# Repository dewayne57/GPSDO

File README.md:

# GPSDO (GPS Disciplined Oscillator)

This repository contains a hardware and firmware design for a GPS-disciplined oscillator (GPSDO). The system uses
a local oven-controlled crystal oscillator (OCXO) disciplined by a GPS reference (1PPS and time) via a digital control
loop implemented on a PIC microcontroller.

Purpose: provide a compact, buildable GPSDO that combines the short-term stability of an OCXO with the long-term
accuracy of GPS. The design favors through-hole assembly and flexible OCXO support so hobbyists and technicians can
adapt the board to available oscillators.

**Repository layout**
- `Hardware/`: KiCad schematics and PCB files, and OCXO compatibility notes.
- `Software/`: PIC firmware source (`main.c`, `isr.c`, config and peripheral drivers).

**Key features**
- Uses a PIC18F series microcontroller for the digital control loop and measurement counters.
- Supports 5 V and 12 V OCXO modules with jumper-selectable scaling.
- External DAC (12-bit) for fine VCO control; optional use of OCXO internal reference.
- Sine-to-square conversion option for sine-output OCXOs.
- Outputs: 10 MHz (square), 1PPS, and serial time/status (where supported).

Hardware notes
- OCXO compatibility: designed for OCXO modules that expose a VCO (frequency adjust) input. Modules without a VCO
	pin are not supported.
- Recommended OCXO families (examples): Bliley N47/NV47, IsoTemp 141 A/N, Vectron C4550, Oscilloquartz 8663.
- VCO adjustment: typical adjustment ranges are on the order of ±0.4 to ±1.0 ppm. For a 10 MHz OCXO, ±0.4 ppm
	corresponds to about ±4 Hz of pull range.
- Voltage reference: jumpers allow either the OCXO's onboard reference or the microcontroller-supplied reference to be
	used for VCO control circuitry.
- Power: supports 5 V and 12 V OCXO modules. The design omits 3.3 V OCXO variants to keep voltage-scaling circuitry
	simpler.

Firmware and control
- The PIC microcontroller implements the digital disciplining loop: it measures phase/frequency against GPS 1PPS and
	computes corrections applied through the DAC to the OCXO VCO input.
- Communication: firmware includes basic status reporting via serial (see `Software/` source files).

## Theory of Operation

Overview
- The system uses the PIC18F's high-speed signal acquisition timer/counter to measure the OCXO frequency against the GPS
	1PPS reference. The 10 MHz output from the OCXO (after conditioning through comparator or buffering as needed) is fed
	into the controller's counter. Each rising edge of the 1PPS signal triggers a capture of the counter value.

Measurement and error calculation
- The counter measurement produces the number of 10 MHz cycles counted during one 1-second interval. For an ideal
	10 MHz oscillator the measured count is 10,000,000. The firmware computes the frequency error as:

	`error = measured_count - 10,000,000`

- Control action sign: when `measured_count > 10,000,000` (oscillator fast) the firmware decreases the DAC output
	(reducing VCO control voltage) to lower the oscillator frequency. Conversely, when `measured_count < 10,000,000`
	(oscillator slow) the firmware increases the DAC output to raise the frequency.

Resolution and averaging
- A single 1-second count has 1 Hz quantization (one extra or missing cycle = ±1 Hz). Because the OCXO VCO pull range
	is often a few Hz, and long-term stability targets are well below 1 Hz, the firmware uses averaging and filtering
	across multiple 1‑second samples to resolve sub-Hz frequency offsets. Averaging N seconds reduces quantization noise by
	roughly `1/sqrt(N)` for uncorrelated noise and linearly for simple accumulation.

Digital control loop
- The control loop is implemented in firmware and is PID-like: it applies a proportional term (responds to the
	instantaneous frequency error), an integral term (eliminates steady-state offset over time) and optional damping
	(derivative-like or filtered difference) to stabilize transient responses.
- To avoid overshoot and instability, the loop includes:
	- limited update rate and maximum DAC-step per update,
	- anti-windup on the integrator when the DAC saturates,
	- configurable loop bandwidth (slow for best long-term stability, faster during initial acquisition).

Noise and spurious rejection
- Input conditioning: if the OCXO provides a sine output, it is converted to a clean logic edge via the comparator and
	Schmitt trigger chain (comparator `U401`, logic buffers), which reduces timing jitter and false counts.
- Outlier rejection: the firmware detects and ignores single-sample glitches (spikes) using median filters, clamp
	thresholds, or by discarding samples with implausible changes.
- Low-pass filtering: measurement samples are filtered (moving average or IIR) before being fed into the control law to
	reject short-term noise and spurious phase jitter from the GPS receiver or RF pickup.

DAC mapping and VCO sensitivity
- The external DAC (12-bit) produces the control voltage applied to the OCXO VCO pin (optionally scaled by jumper
	networks for 5/12 V OCXOs). The frequency change per DAC LSB depends on the OCXO sensitivity (Hz per volt). The
	firmware maps desired frequency correction to DAC steps and can be configured for the measured sensitivity of a
	particular OCXO.
- Because frequency pull is small (few Hz), the DAC mapping and loop gains are tuned to provide fine, stable control
	without hunting.

Holdover and failure modes
- If GPS is lost, the firmware stops updating the DAC with GPS-derived corrections and enters a holdover mode. During
	holdover the DAC will be left at its last value.
- GPS lock is indicated by a front-panel LED.  If the GPS lock is lost, the operator should take the appropriate 
    actions to reposition or repair the GPS antenna.

Practical notes
- One-count resolution at 10 MHz corresponds to 1 Hz. To achieve sub-Hz apparent resolution the firmware averages and
	filters multiple 1PPS-captured counts before making DAC adjustments.
- Avoid using OCXO modules without an external VCO adjust pin — they cannot be disciplined by this design.
- Proper grounding, shielding, and clean supply rails reduce spurious counts and improve loop stability.

Build and usage
- Hardware: assemble the board following the silkscreen and BOM in `Hardware/`. Populate only the sections required for
	your chosen OCXO (jumper options allow omitting comparator/driver or scaling components).
- Antenna: mount the GPS antenna with a clear sky view; use a low-loss cable and proper grounding/lightning protection.
- Initial setup:
	1. Install firmware from `Software/` using a PIC programmer supporting the PIC18F family.
	2. Connect GPS antenna and power the board.
	3. Wait for GPS lock and allow the disciplining loop to converge (can take minutes to hours depending on configuration).
- Holdover: if GPS signal is lost, the OCXO runs free; holdover performance depends on the OCXO quality.

Testing and calibration
- Verify 1PPS and 10 MHz outputs with a frequency counter or scope.
- Observe DAC control voltage and confirm it stays within expected range while disciplining.
- Perform a holdover test by disconnecting GPS and measuring drift over a chosen interval.

Design considerations and limitations
- GPS vulnerability: system depends on GPS; consider anti-spoofing/jamming mitigation for critical deployments.
- Environmental sensitivity: OCXO performance varies with temperature — good thermal control improves holdover.

Contributing
If you improve the firmware, PCB, or documentation, please open an issue or a pull request. Include a short description
of your changes and validation steps.

License and credits
- This entire repository (software and hardware design files) is licensed under the Apache License, Version 2.0. See
  `LICENSE` at the repository root for the full text.
- If you incorporate third-party components with separate license requirements, include their required notices and
  follow the terms of those licenses.

Files of interest
- `Hardware/GPSDO.kicad_sch`, `Hardware/GPSDO.kicad_pcb`: primary schematic and PCB.
- `Software/main.c`, `Software/isr.c`, `Software/config.h`: firmware entry points and configuration.

Contact
Open issues in this repository or contact the author via the repository metadata for questions and contribution guidance.

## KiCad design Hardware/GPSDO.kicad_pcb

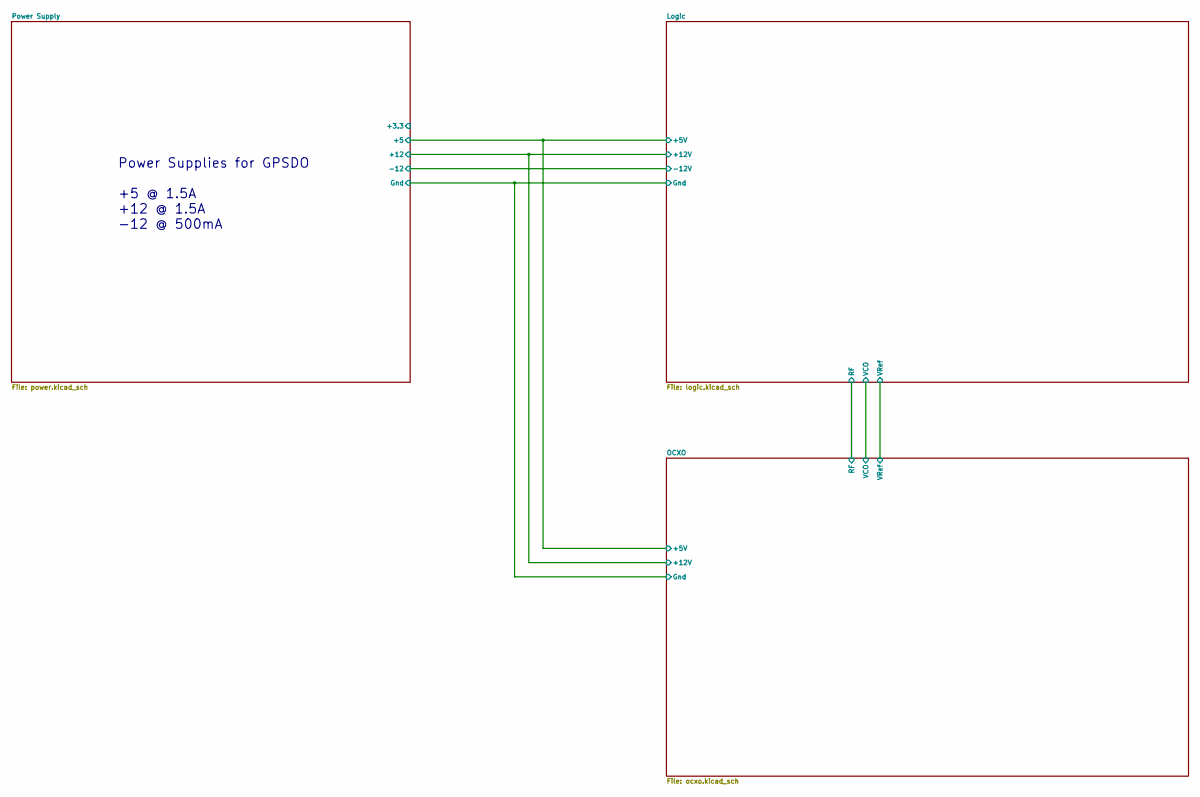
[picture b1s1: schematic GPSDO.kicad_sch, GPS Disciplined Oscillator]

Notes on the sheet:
Power Supplies for GPSDO +5 @ 1.5A +12 @ 1.5A -12 @ 500mA

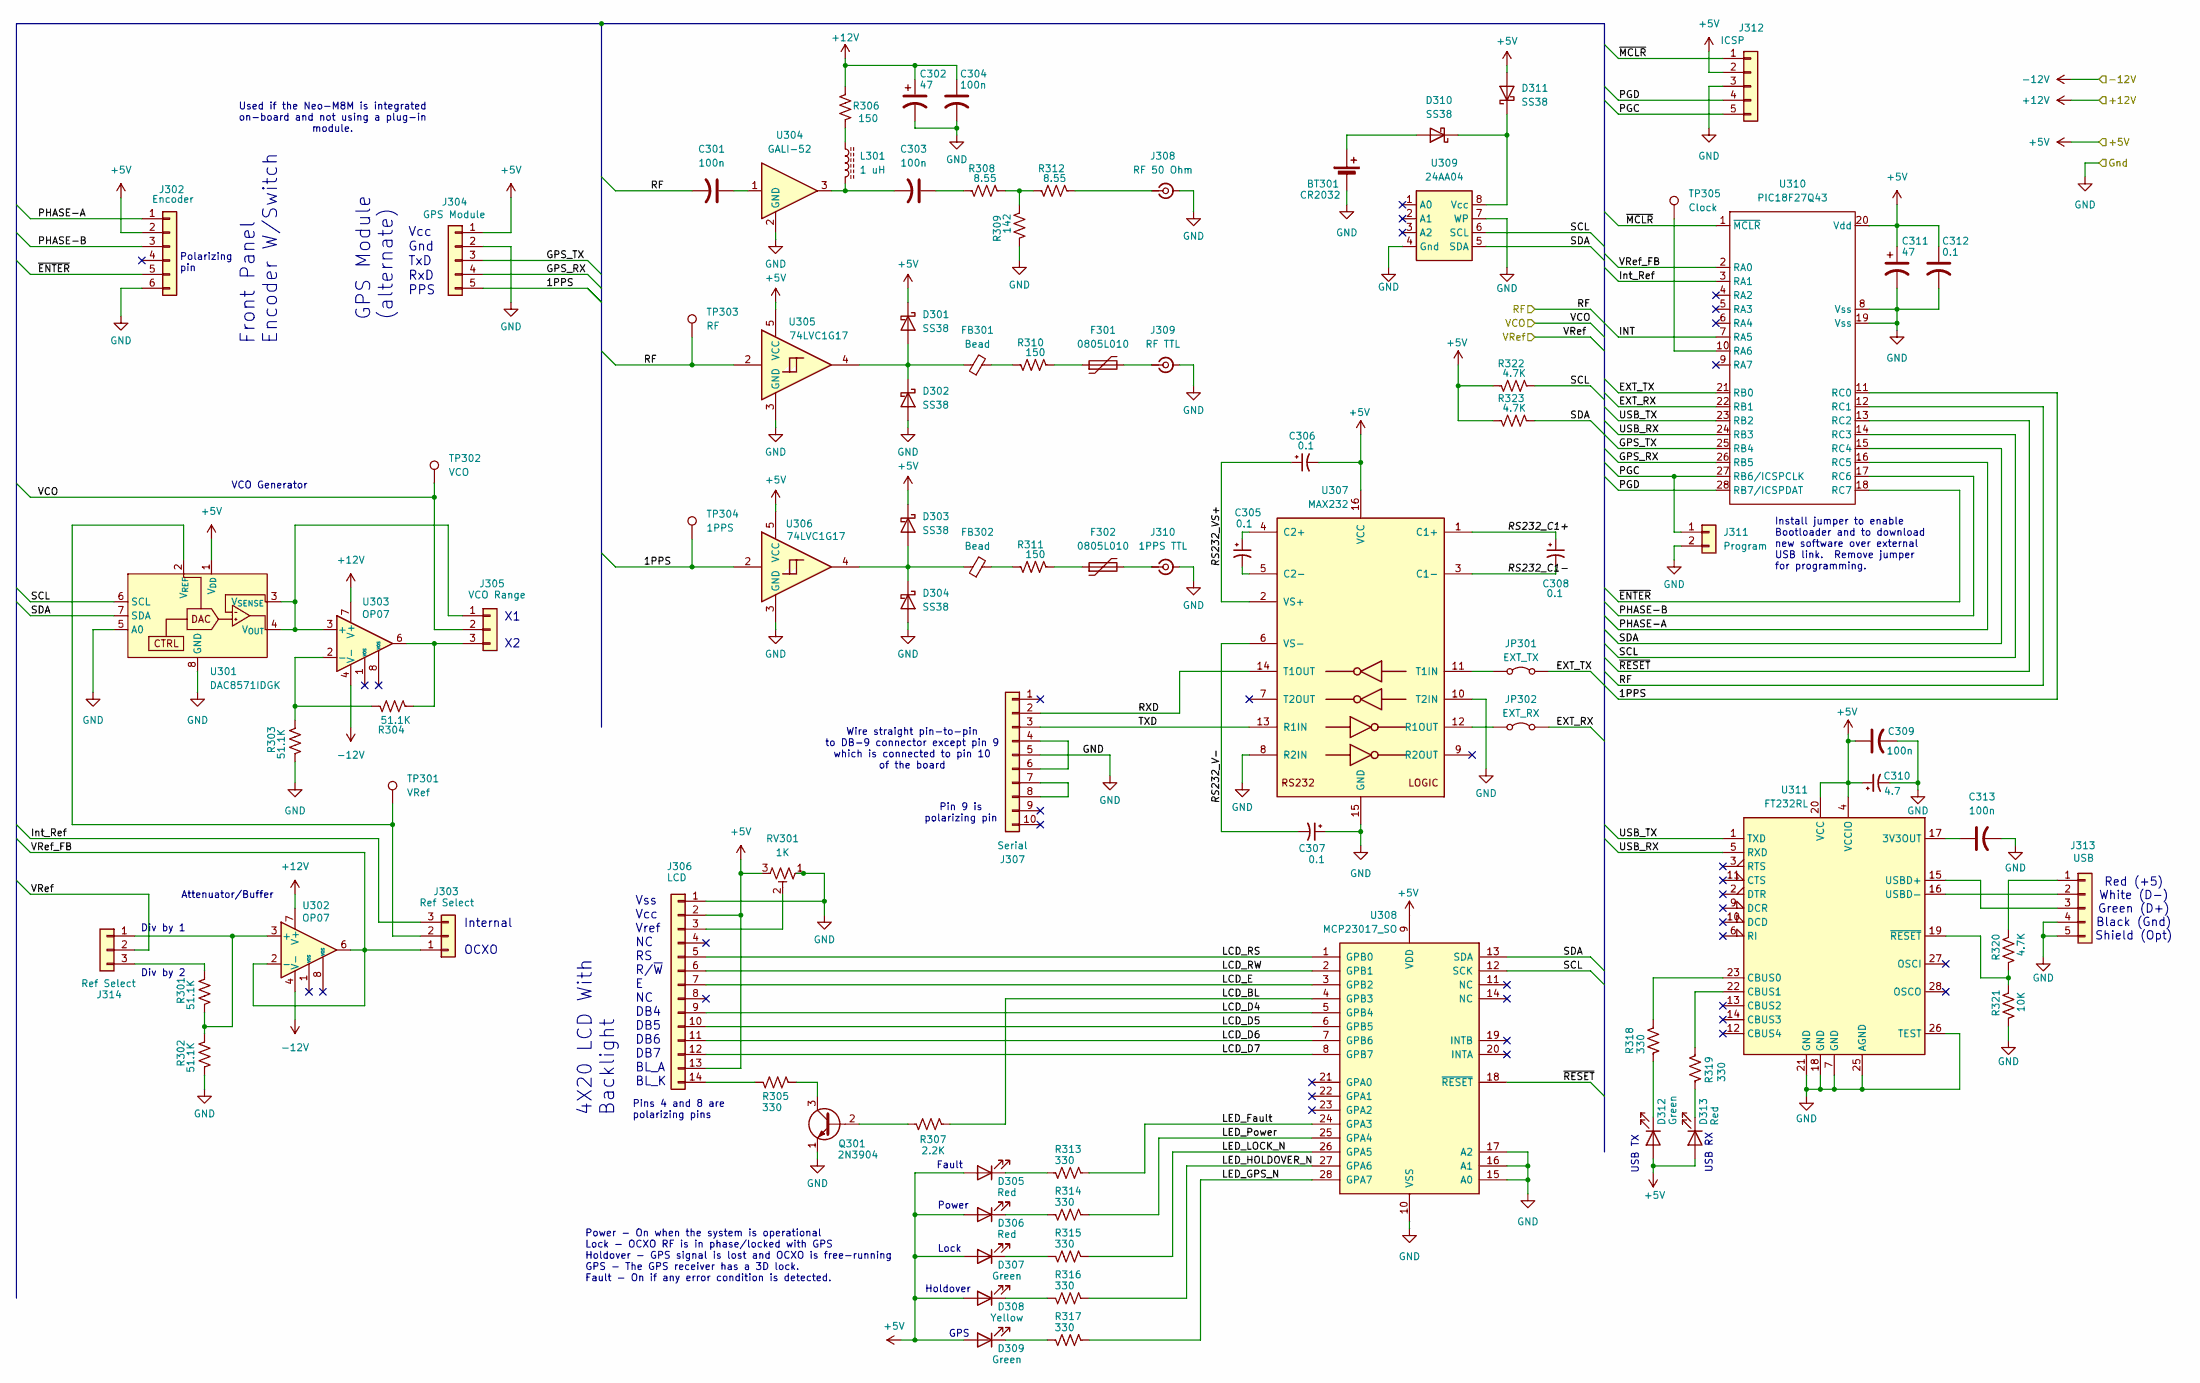
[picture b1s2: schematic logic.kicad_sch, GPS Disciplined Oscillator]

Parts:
BT301: CR2032; Battery_Panasonic_CR2032-HFN_Horizontal_CircularHoles
C301, C303, C304, C309, C313: 100n; C_0603_1608Metric_Pad1.08x0.95mm_HandSolder
C302, C311: 47; CP_Elec_8x6.9
C305, C306, C307, C308: 0.1; CP_Elec_4x5.4
C310: 4.7; CP_Elec_6.3x5.4
C312: 0.1; C_0603_1608Metric_Pad1.08x0.95mm_HandSolder
D301, D302, D303, D304, D310, D311: SS38; D_SMB_Handsoldering
D305, D306, D313: Red; LED_D3.0mm_Horizontal_O3.81mm_Z2.0mm
D307, D309, D312: Green; LED_D3.0mm_Horizontal_O3.81mm_Z2.0mm
D308: Yellow; LED_D3.0mm_Horizontal_O3.81mm_Z2.0mm
F301, F302: 0805L010; R_0805_2012Metric_Pad1.20x1.40mm_HandSolder
FB301, FB302: Bead; L_0805_2012Metric_Pad1.15x1.40mm_HandSolder
J302: Encoder; PinHeader_1x06_P2.54mm_Vertical
J303, J314: Ref Select; PinHeader_1x03_P2.54mm_Vertical
J304: GPS Module; PinHeader_1x05_P2.54mm_Vertical
J305: VCO Range; PinHeader_1x03_P2.54mm_Vertical
J306: LCD; PinHeader_1x14_P2.54mm_Vertical
J307: Serial; PinHeader_1x10_P2.54mm_Vertical
J308: RF 50 Ohm; SMA_Amphenol_901-144_Vertical
J309: RF TTL; SMA_Amphenol_901-144_Vertical
J310: 1PPS TTL; SMA_Amphenol_901-144_Vertical
J311: Program; PinHeader_1x02_P2.54mm_Vertical
J312: ICSP; PinHeader_1x05_P2.54mm_Vertical
J313: USB; PinSocket_1x05_P2.54mm_Vertical
JP301: EXT_TX; R_Box_L26.0mm_W5.0mm_P20.00mm
JP302: EXT_RX; R_Box_L26.0mm_W5.0mm_P20.00mm
L301: 1 uH; L_1206_3216Metric_Pad1.42x1.75mm_HandSolder
Q301: 2N3904; TO-92L_HandSolder
R301, R302, R303, R304: 51.1K; R_0805_2012Metric_Pad1.20x1.40mm_HandSolder
R305, R313, R314, R315, R316, R317, R318, R319: 330; R_0805_2012Metric_Pad1.20x1.40mm_HandSolder
R306, R310, R311: 150; R_0805_2012Metric_Pad1.20x1.40mm_HandSolder
R307: 2.2K; R_0805_2012Metric_Pad1.20x1.40mm_HandSolder
R308, R312: 8.55; R_0805_2012Metric_Pad1.20x1.40mm_HandSolder
R309: 142; R_0805_2012Metric_Pad1.20x1.40mm_HandSolder
R320, R322, R323: 4.7K; R_0805_2012Metric_Pad1.20x1.40mm_HandSolder
R321: 10K; R_0805_2012Metric_Pad1.20x1.40mm_HandSolder
RV301: 1K; Potentiometer_Bourns_3266W_Vertical
TP301: VRef; TestPoint_Bridge_Pitch2.54mm_Drill1.0mm
TP302: VCO; TestPoint_Bridge_Pitch2.54mm_Drill1.0mm
TP303: RF; TestPoint_Bridge_Pitch2.54mm_Drill1.0mm
TP304: 1PPS; TestPoint_Bridge_Pitch2.54mm_Drill1.0mm
TP305: Clock; TestPoint_Bridge_Pitch2.54mm_Drill1.0mm
U301: DAC8571IDGK; MSOP-8_3x3mm_P0.65mm
U302, U303: OP07; SOIC-8_3.9x4.9mm_P1.27mm
U304: GALI-52; SOT-89-3
U305, U306: 74LVC1G17; SOT-353_SC-70-5
U307: MAX232; DIP-16_W7.62mm_LongPads
U308: MCP23017_SO; SOIC-28W_7.5x17.9mm_P1.27mm
U309: 24AA04; SOIC-8_5.3x6.2mm_P1.27mm
U310: PIC18F27Q43; SOIC-28W_7.5x18.7mm_P1.27mm
U311: FT232RL; SSOP-28_5.3x10.2mm_P0.65mm

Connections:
+5V: C306.2, C309.1, C310.1, C311.1, C312.1, D301.1 (K), D303.1 (K), D305.2 (A), D306.2 (A), D307.2 (A), D308.2 (A), D309.2 (A), D311.2 (A), D312.2 (A), D313.2 (A), J302.2, J304.1, J306.2, J306.13, J312.2, R322.1, R323.1, RV301.3, U301.1 (V_{DD}), U305.5 (VCC), U306.5 (VCC), U307.16 (VCC), U308.9 (VDD), U310.20 (Vdd), U311.4 (VCCIO), U311.20 (VCC); also elsewhere on the board
+12V: C302.1, C304.1, R306.1, U302.7 (V+), U303.7 (V+); also elsewhere on the board
-12V: U302.4 (V-), U303.4 (V-); also elsewhere on the board
/Logic/1PPS: J304.5, TP304.1, U306.2, U310.11 (RC0)
/Logic/EXT_RX: JP302.2 (B), U310.22 (RB1)
/Logic/EXT_TX: JP301.2 (B), U310.21 (RB0)
/Logic/GPS_RX: J304.4, U310.26 (RB5)
/Logic/GPS_TX: J304.3, U310.25 (RB4)
/Logic/INT: U310.7 (RA5)
/Logic/Int_Ref: J303.3, U310.3 (RA1)
/Logic/LCD_BL: R307.2, U308.4 (GPB3)
/Logic/LCD_D4: J306.9, U308.5 (GPB4)
/Logic/LCD_D5: J306.10, U308.6 (GPB5)
/Logic/LCD_D6: J306.11, U308.7 (GPB6)
/Logic/LCD_D7: J306.12, U308.8 (GPB7)
/Logic/LCD_E: J306.7, U308.3 (GPB2)
/Logic/LCD_RS: J306.5, U308.1 (GPB0)
/Logic/LCD_RW: J306.6, U308.2 (GPB1)
/Logic/LED_Fault: R313.2, U308.24 (GPA3)
/Logic/LED_GPS_N: R317.2, U308.28 (GPA7)
/Logic/LED_HOLDOVER_N: R316.2, U308.27 (GPA6)
/Logic/LED_LOCK_N: R315.2, U308.26 (GPA5)
/Logic/LED_Power: R314.2, U308.25 (GPA4)
/Logic/PGC: J311.1, J312.5, U310.27 (RB6/ICSPCLK)
/Logic/PGD: J312.4, U310.28 (RB7/ICSPDAT)
/Logic/PHASE-A: J302.1, U310.16 (RC5)
/Logic/PHASE-B: J302.3, U310.17 (RC6)
/Logic/RF: C301.2, TP303.1, U305.2, U310.12 (RC1); also elsewhere on the board
/Logic/RS232_C1+: C308.1, U307.1 (C1+)
/Logic/RS232_C1-: C308.2, U307.3 (C1-)
/Logic/RS232_V-: C307.2, U307.6 (VS-)
/Logic/RS232_VS+: C306.1, U307.2 (VS+)
/Logic/RXD: J307.2, U307.14 (T1OUT)
/Logic/SCL: R322.2, U301.6 (SCL), U308.12 (SCK), U309.6 (SCL), U310.14 (RC3)
/Logic/SDA: R323.2, U301.7 (SDA), U308.13 (SDA), U309.5 (SDA), U310.15 (RC4)
/Logic/TXD: J307.3, U307.13 (R1IN)
/Logic/USB_RX: U310.24 (RB3), U311.5 (RXD)
/Logic/USB_TX: U310.23 (RB2), U311.1 (TXD)
/Logic/VCO: J305.2, TP302.1; also elsewhere on the board
/Logic/VRef: J314.2; also elsewhere on the board
/Logic/VRef_FB: J303.1, U302.2 (-), U302.6, U310.2 (RA0)
/Logic/~ENTER: J302.5, U310.18 (RC7)
/Logic/~MCLR: J312.1, U310.1 (~MCLR)
/Logic/~RESET: U308.18 (~RESET), U310.13 (RC2)
GND: BT301.2 (-), C302.2, C304.2, C307.1, C309.2, C310.2, C311.2, C312.2, C313.2, D302.2 (A), D304.2 (A), J302.6, J304.2, J306.1, J307.5, J308.2 (Ext), J309.2 (Ext), J310.2 (Ext), J311.2, J312.3, J313.4, J313.5, Q301.1 (E), R302.1, R303.1, R309.1, R321.2, RV301.1, U301.5 (A0), U301.8 (GND), U304.2 (GND), U305.3 (GND), U306.3 (GND), U307.8 (R2IN), U307.10 (T2IN), U307.15 (GND), U308.10 (VSS), U308.15 (A0), U308.16 (A1), U308.17 (A2), U309.4 (Gnd), U309.7 (WP), U310.8 (Vss), U310.19 (Vss), U311.7 (GND), U311.18 (GND), U311.21 (GND), U311.25 (AGND), U311.26 (TEST); also elsewhere on the board
unnamed: BT301.1 (+), D310.2 (A)
unnamed: C301.1, U304.1
unnamed: C303.1, R308.1
unnamed: C303.2, L301.2, U304.3
unnamed: D301.2 (A), D302.1 (K), FB301.1, U305.4
unnamed: D303.2 (A), D304.1 (K), FB302.1, U306.4
unnamed: D305.1 (K), R313.1
unnamed: D306.1 (K), R314.1
unnamed: D307.1 (K), R315.1
unnamed: D308.1 (K), R316.1
unnamed: D309.1 (K), R317.1
unnamed: D310.1 (K), D311.1 (K), U309.8 (Vcc)
unnamed: D312.1 (K), R318.1
unnamed: D313.1 (K), R319.1
unnamed: F301.1, R310.2
unnamed: F302.1, R311.2
unnamed: FB301.2, R310.1
unnamed: FB302.2, R311.1
unnamed: J303.2, TP301.1, U301.2 (V_{REF})
unnamed: J305.1, U301.3 (V_{SENSE}), U301.4 (V_{OUT}), U303.3 (+)
unnamed: J305.3, R304.1, U303.6
unnamed: J306.3, RV301.2
unnamed: J306.14, R305.1
unnamed: J307.4, J307.6
unnamed: J307.7, J307.8
unnamed: J308.1 (In), R312.2
unnamed: F301.2, J309.1 (In)
unnamed: F302.2, J310.1 (In)
unnamed: J313.1, R320.1
unnamed: J313.2, U311.16 (USBD-)
unnamed: J313.3, U311.15 (USBD+)
unnamed: J314.1, R301.1, R302.2, U302.3 (+)
unnamed: J314.3, R301.2
unnamed: JP301.1 (A), U307.11 (T1IN)
unnamed: JP302.1 (A), U307.12 (R1OUT)
unnamed: L301.1, R306.2
unnamed: Q301.2 (B), R307.1
unnamed: Q301.3 (C), R305.2
unnamed: R308.2, R309.2, R312.1
unnamed: R303.2, R304.2, U303.2 (-)
unnamed: C305.1, U307.4 (C2+)
unnamed: C305.2, U307.5 (C2-)
unnamed: TP305.1, U310.10 (RA6)
unnamed: C313.1, U311.17 (3V3OUT)
unnamed: R318.2, U311.23 (CBUS0)
unnamed: R319.2, U311.22 (CBUS1)
unnamed: R320.2, R321.1, U311.19 (~RESET)

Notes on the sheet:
USB RX
GPS
4X20 LCD With Backlight
Div by 1 Div by 2
Install jumper to enable Bootloader and to download new software over external USB link. Remove jumper for programming.
Vcc Gnd TxD RxD PPS
X1 X2
Internal OCXO
Red (+5) White (D-) Green (D+) Black (Gnd) Shield (Opt)
Lock
Pins 4 and 8 are polarizing pins
Vss Vcc Vref NC RS R/~{W} E NC DB4 DB5 DB6 DB7 BL_A BL_K
Used if the Neo-M8M is integrated on-board and not using a plug-in module.
USB TX
Pin 9 is polarizing pin
Wire straight pin-to-pin to DB-9 connector except pin 9 which is connected to pin 10 of the board
Power
Fault
Front Panel Encoder W/Switch
Power - On when the system is operational Lock - OCXO RF is in phase/locked with GPS Holdover - GPS signal is lost and OCXO is free-running GPS - The GPS receiver has a 3D lock. Fault - On if any error condition is detected.
Attenuator/Buffer
Polarizing pin
VCO Generator
GPS Module (alternate)
Holdover

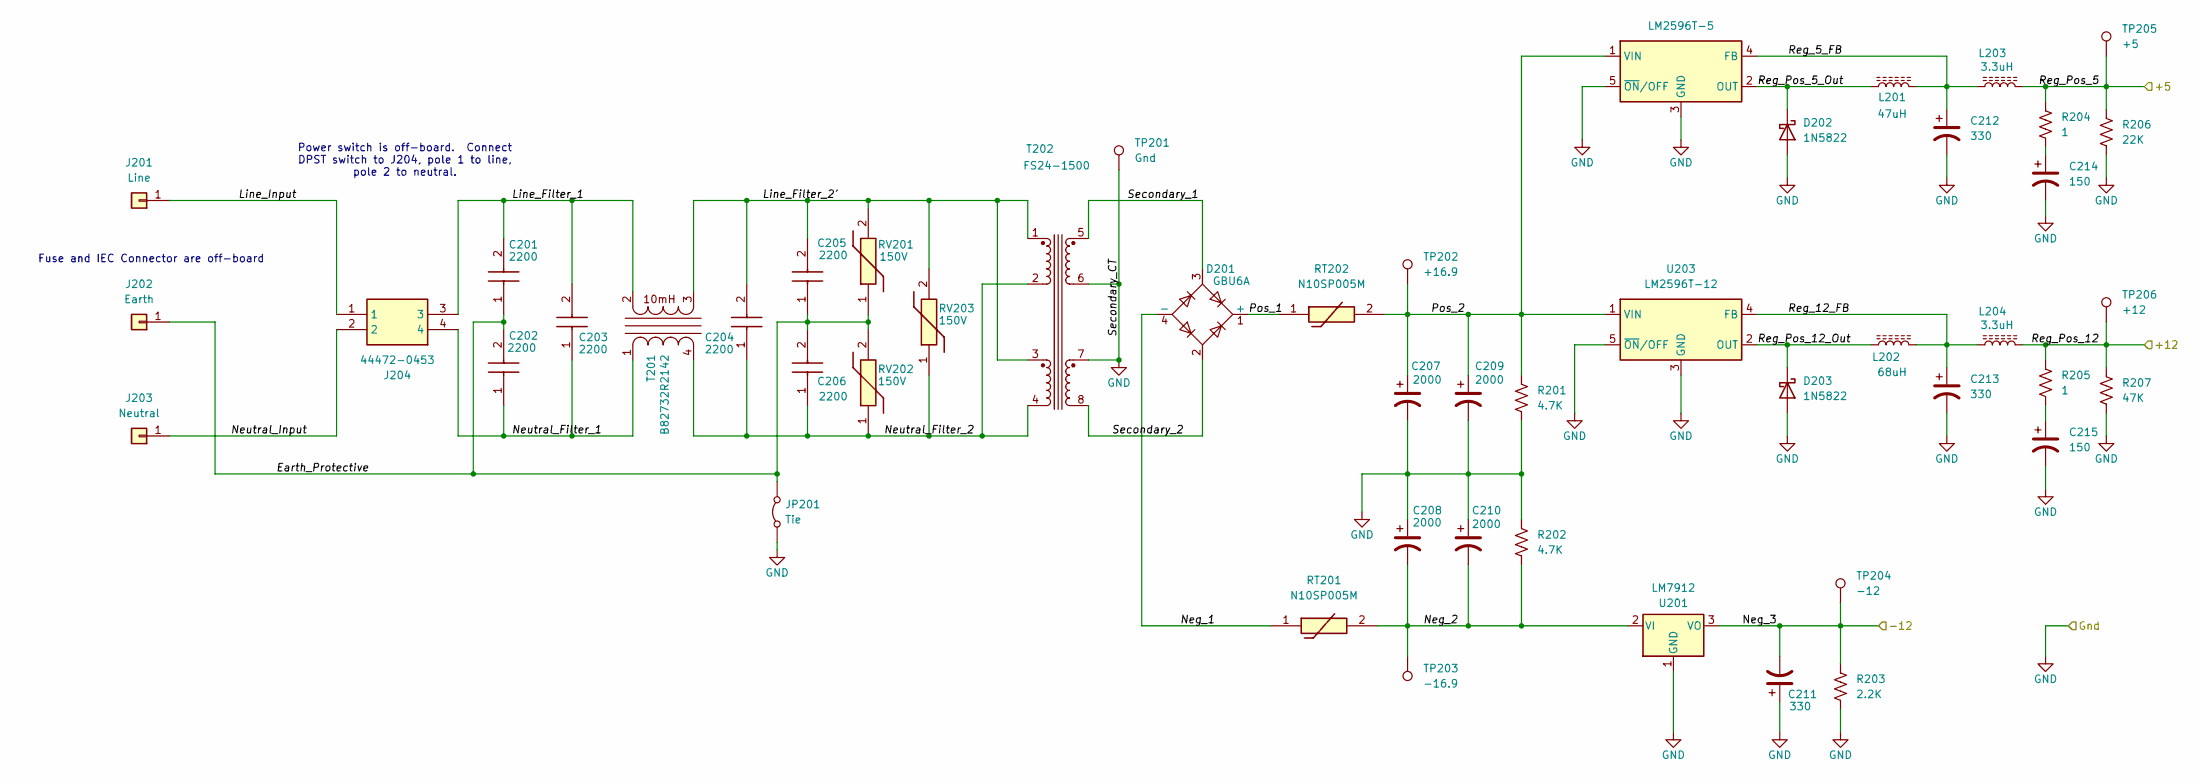
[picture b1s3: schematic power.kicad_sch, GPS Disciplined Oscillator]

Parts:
C201, C202, C203, C204, C205, C206: 2200; C731U222MSVDBAWL35; Mouser Part Number 80-C731U222MSVDBWL35
C207, C208, C209, C210: 2000; CP_Elec_18x22
C211, C212, C213: 330; CP_Elec_10x10.5
C214, C215: 150; CP_Elec_10x10
D201: GBU6A; Diode_Bridge_Vishay_GBU
D202, D203: 1N5822; D_SOD-128
J201: Line; Amp Faston 250 THT
J202: Earth; Amp Faston 250 THT
J203: Neutral; Amp Faston 250 THT
J204: 44472-0453; 44472-04YY; Mouser Part Number 538-44472-0453
JP201: Tie; SolderJumper-2_P1.3mm_Bridged_RoundedPad1.0x1.5mm
L201: 47uH; Bourns PM5022
L202: 68uH; Bourns PM5022
L203, L204: 3.3uH; Bourns SDE04030
R201, R202: 4.7K; R_0805_2012Metric_Pad1.20x1.40mm_HandSolder
R203: 2.2K; R_0805_2012Metric_Pad1.20x1.40mm_HandSolder
R204, R205: 1; R_0805_2012Metric_Pad1.20x1.40mm_HandSolder
R206: 22K; R_0805_2012Metric_Pad1.20x1.40mm_HandSolder
R207: 47K; R_0805_2012Metric_Pad1.20x1.40mm_HandSolder
RT201, RT202: N10SP005M; Mouser Part Number 603-N10SP005M
RV201, RV202, RV203: 150V; MOV20D241KKTR; Mouser Part Number 652-MOV-20D241KKTR
T201: B82732R2142; TDK B82732R Series
T202: FS24-1500; FS-36VA
TP201: Gnd; TestPoint_Bridge_Pitch2.54mm_Drill1.0mm
TP202: +16.9; TestPoint_Bridge_Pitch2.54mm_Drill1.0mm
TP203: -16.9; TestPoint_Bridge_Pitch2.54mm_Drill1.0mm
TP204: -12; TestPoint_Bridge_Pitch2.54mm_Drill1.0mm
TP205: +5; TestPoint_Bridge_Pitch2.54mm_Drill1.0mm
TP206: +12; TestPoint_Bridge_Pitch2.54mm_Drill1.0mm
U201: LM7912; TO-220-3_Vertical
U202: LM2596T-5; TO-220-5_P3.4x3.7mm_StaggerOdd_Lead3.8mm_Vertical
U203: LM2596T-12; TO-220-5_P3.4x3.7mm_StaggerOdd_Lead3.8mm_Vertical

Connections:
+5V: L203.2, R204.1, R206.1, TP205.1; also elsewhere on the board
+12V: L204.2, R205.1, R207.1, TP206.1; also elsewhere on the board
-12V: C211.2, R203.1, TP204.1, U201.3 (VO); also elsewhere on the board
/Power Supply/Earth_Protective: C201.1, C202.2, C205.1, C206.2, J202.1, JP201.2 (B), RV201.1, RV202.2
/Power Supply/Line_Filter_1: C201.2, C203.2, J204.3, T201.2
/Power Supply/Line_Filter_2': C204.2, C205.2, RV201.2, RV203.2, T201.3, T202.1, T202.3
/Power Supply/Line_Input: J201.1, J204.1
/Power Supply/Neg_1: D201.4 (-), RT201.1
/Power Supply/Neg_2: C208.2, C210.2, R202.2, RT201.2, TP203.1, U201.2 (VI)
/Power Supply/Neutral_Filter_1: C202.1, C203.1, J204.4, T201.1
/Power Supply/Neutral_Filter_2: C204.1, C206.1, RV202.1, RV203.1, T201.4, T202.2, T202.4
/Power Supply/Neutral_Input: J203.1, J204.2
/Power Supply/Pos_1: D201.1 (+), RT202.1
/Power Supply/Pos_2: C207.1, C209.1, R201.1, RT202.2, TP202.1, U202.1 (VIN), U203.1 (VIN)
/Power Supply/Reg_5_FB: C212.1, L201.2, L203.1, U202.4 (FB)
/Power Supply/Reg_12_FB: C213.1, L202.2, L204.1, U203.4 (FB)
/Power Supply/Reg_Pos_5_Out: D202.1 (K), L201.1, U202.2 (OUT)
/Power Supply/Reg_Pos_12_Out: D203.1 (K), L202.1, U203.2 (OUT)
/Power Supply/Secondary_1: D201.3, T202.5
/Power Supply/Secondary_2: D201.2, T202.8
GND: C207.2, C208.1, C209.2, C210.1, C211.1, C212.2, C213.2, C214.2, C215.2, D202.2 (A), D203.2 (A), JP201.1 (A), R201.2, R202.1, R203.2, R206.2, R207.2, T202.6, T202.7, TP201.1, U201.1 (GND), U202.3 (GND), U202.5 (~ON/OFF), U203.3 (GND), U203.5 (~ON/OFF); also elsewhere on the board
unnamed: C214.1, R204.2
unnamed: C215.1, R205.2

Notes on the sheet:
Power switch is off-board. Connect DPST switch to J204, pole 1 to line, pole 2 to neutral.
Fuse and IEC Connector are off-board

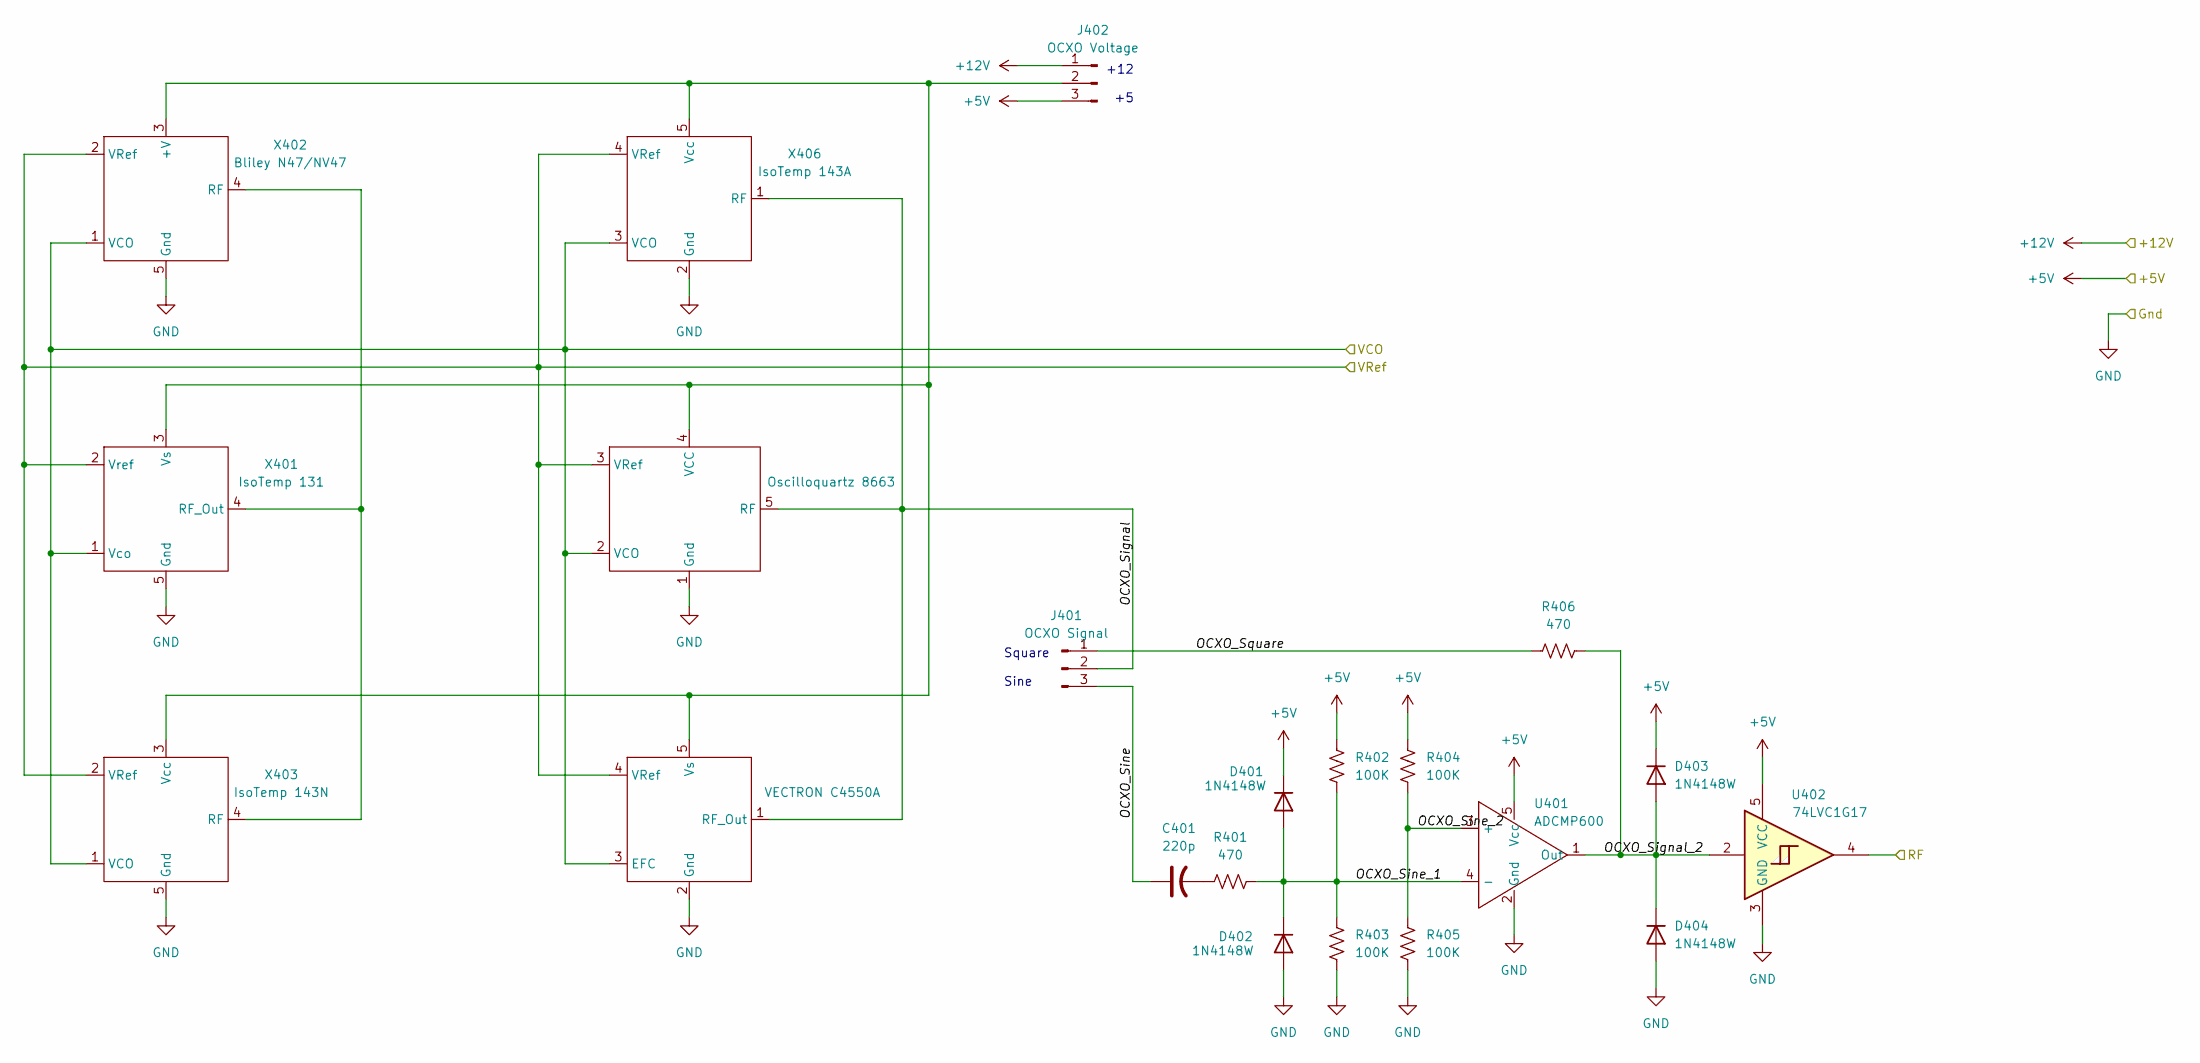
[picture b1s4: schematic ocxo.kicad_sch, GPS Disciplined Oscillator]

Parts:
C401: 220p; C_0603_1608Metric_Pad1.08x0.95mm_HandSolder
D401, D402, D403, D404: 1N4148W; D_SOD-323_HandSoldering
J401: OCXO Signal; PinHeader_1x03_P2.54mm_Vertical
J402: OCXO Voltage; PinHeader_1x03_P2.54mm_Vertical
R401, R406: 470; R_0805_2012Metric_Pad1.20x1.40mm_HandSolder
R402, R403, R404, R405: 100K; R_0805_2012Metric_Pad1.20x1.40mm_HandSolder
U401: ADCMP600; SOT-23-5
U402: 74LVC1G17; SOT-353_SC-70-5
X401: IsoTemp 131; ISOTEMP 131
X402: Bliley N47/NV47; Bliley N47
X403: IsoTemp 143N; ISOTEMP 143N
X404: VECTRON C4550A; VectronC4550-A
X405: Oscilloquartz 8663; OQ8663
X406: IsoTemp 143A; ISOTEMP 143A

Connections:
+5V: D401.1 (K), D403.1 (K), J402.3, R402.2, R404.2, U401.5 (Vcc), U402.5 (VCC); also elsewhere on the board
+12V: J402.1; also elsewhere on the board
/Logic/RF: U402.4; also elsewhere on the board
/Logic/VCO: X401.1 (Vco), X402.1 (VCO), X403.1 (VCO), X404.3 (EFC), X405.2 (VCO), X406.3 (VCO); also elsewhere on the board
/Logic/VRef: X401.2 (Vref), X402.2 (VRef), X403.2 (VRef), X404.4 (VRef), X405.3 (VRef), X406.4 (VRef); also elsewhere on the board
/OCXO/OCXO_Signal: J401.2, X404.1 (RF_Out), X405.5 (RF), X406.1 (RF)
/OCXO/OCXO_Signal_2: D403.2 (A), D404.1 (K), R406.2, U401.1 (Out), U402.2
/OCXO/OCXO_Sine: C401.1, J401.3
/OCXO/OCXO_Sine_1: D401.2 (A), D402.1 (K), R401.2, R402.1, R403.2, U401.4 (-)
/OCXO/OCXO_Sine_2: R404.1, R405.2, U401.3 (+)
/OCXO/OCXO_Square: J401.1, R406.1
GND: D402.2 (A), D404.2 (A), R403.1, R405.1, U401.2 (Gnd), U402.3 (GND), X401.5 (Gnd), X402.5 (Gnd), X403.5 (Gnd), X404.2 (Gnd), X405.1 (Gnd), X406.2 (Gnd); also elsewhere on the board
unnamed: C401.2, R401.1
unnamed: J402.2, X401.3 (Vs), X402.3 (+V), X403.3 (Vcc), X404.5 (Vs), X405.4 (VCC), X406.5 (Vcc)
unnamed: X401.4 (RF_Out), X402.4 (RF), X403.4 (RF)

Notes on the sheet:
+12 +5
Square Sine

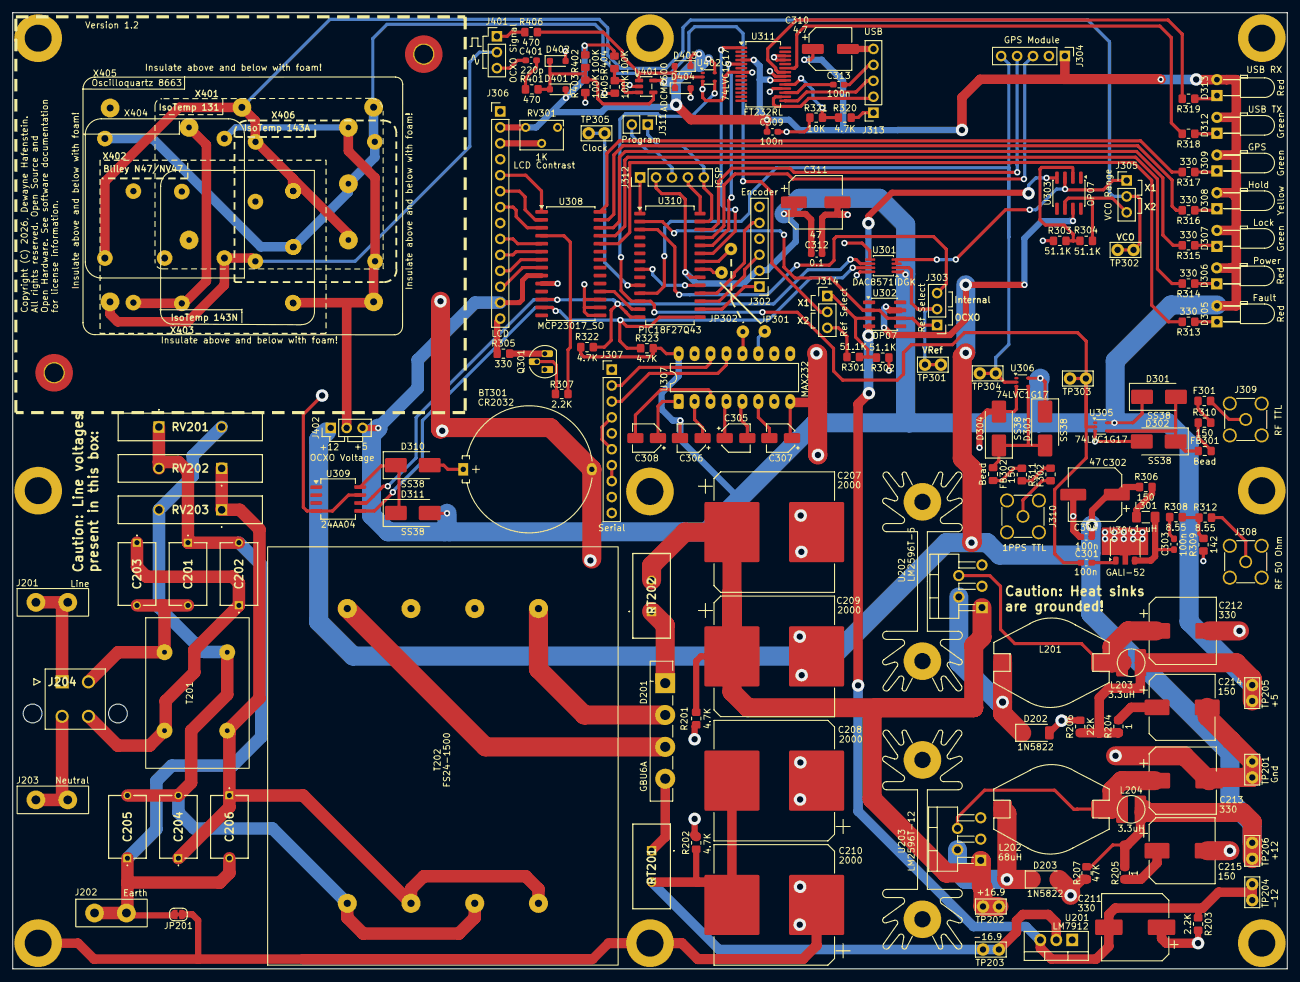
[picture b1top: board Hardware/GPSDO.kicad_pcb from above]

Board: 2 copper layers, 203.2 x 152.4 mm, 157 parts (0 on the bottom side), 115 nets.

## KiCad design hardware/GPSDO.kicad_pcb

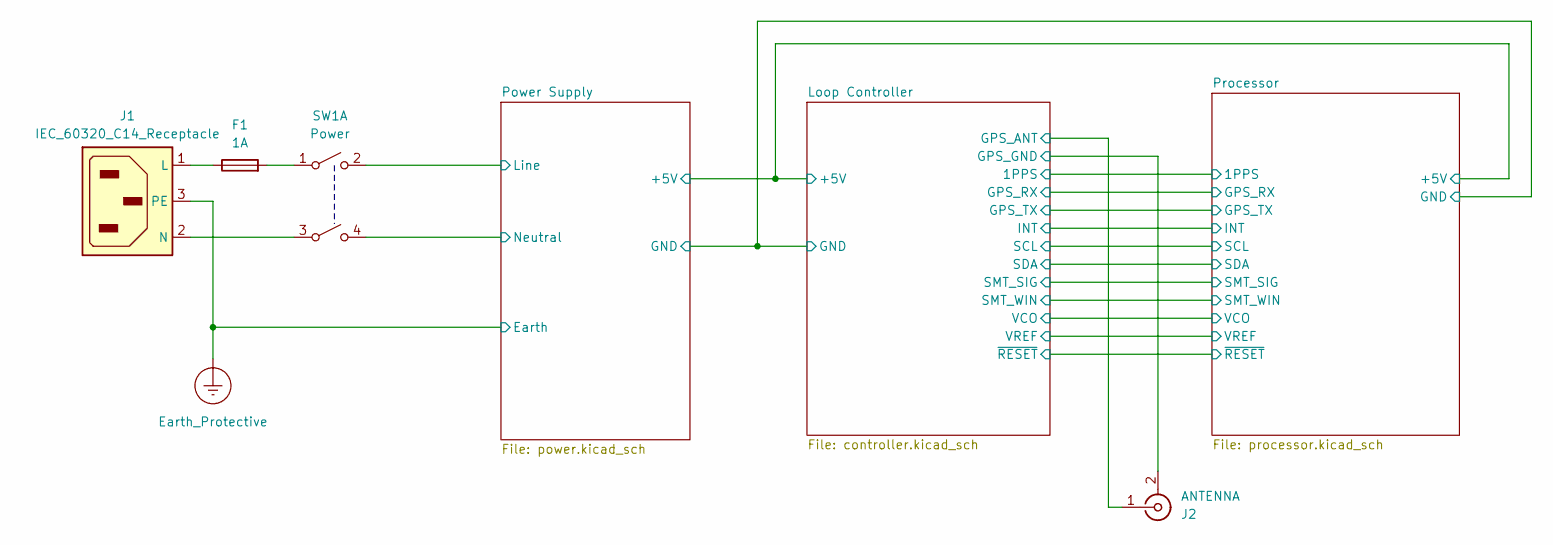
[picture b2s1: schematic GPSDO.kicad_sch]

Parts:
F1: 1A
J1: IEC_60320_C14_Receptacle
J2: ANTENNA
SW1: Power

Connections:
unnamed: F1.1, J1.1 (L)
unnamed: F1.2, SW1.1 (A)
unnamed: J1.2 (N), SW1.3 (A)

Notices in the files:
Software/config.h:
Copyright (c) 2026, Dewayne L. Hafenstein.  All rights reserved.
Licensed under the Apache License, Version 2.0 (the "License");
Hardware/GPSDO.kicad_pcb:
Copyright (C) 2026, Dewayne Hafenstein.
All rights reserved. Open Source and
Open Hardware. See software documentation
